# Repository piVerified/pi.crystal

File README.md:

# pi.crstal

A blinker board that is in thw shape of a crystal! 

---
## 3D

| Top | Bottom |
| :--: | :--: |
|  |  |

---
## KiCAD

| Schematic | PCB |
| :-------: | :-: |
|  | |

---
# BOM
|Name                                       |Purpose                                            |Quantity|Total Cost (USD)|Link                                                                                                                                                                                                                   |Distributor     |
|-------------------------------------------|---------------------------------------------------|--------|----------------|-----------------------------------------------------------------------------------------------------------------------------------------------------------------------------------------------------------------------|----------------|
|PCB (minimum order qty is 5)               |Main Circuitry                                     |5       |10.27           |https://robu.in/cart                                                                                                                                                                                                   |Robu            |
|Jumper Wires (pack of 40)                  |To program the IC via a breadboard and rp2040 setup|1       |0.54            |https://quartzcomponents.com/products/male-to-male-connecting-wires-jumper-wires-set-of-40?variant=45062845464810                                                                                                      |Quartzcomponents|
|CR2032 Battery Button Cell Holder - 20mm   |For hold the cell                                  |5       |0.65            |https://quartzcomponents.com/products/cr2032-battery-button-cell-holder-20mm?variant=45714349555946                                                                                                                    |Quartzcomponents|
|LDR Sensor (Light Dependent Resistor) - 5mm|Acts as a interface button                         |10      |0.50            |https://quartzcomponents.com/products/ldr-light-dependent-resistor-5mm?variant=31898051543175                                                                                                                          |Quartzcompenets |
|ATTINY85-20U                               |To intiate the blinig sequence                     |2       |5.08            |https://quartzcomponents.com/products/attiny85-8-bit-avr-microcontroller?variant=33590640345223                                                                                                                        |Quartzcompenets |
|Resistor (pack of 50)                      |to protect the led from current spikes             |1       |1.50            |https://www.flipkart.com/samaes-50-pics-10-ohm-1-watt-5-resistors-fixed-resistor/p/itm472d700363929?pid=RESG6HFFYTRZVUPM&lid=LSTRESG6HFFYTRZVUPM869DSI&marketplace=FLIPKART&pageUID=1775637263894                      |Flipkart        |
|Coin Cell (pack of 5)                      |to power the ckt                                   |1       |1.66            |https://www.flipkart.com/panasonic-cr-2032-battery/p/itmbd0412fc6ad6a?pid=ACCFZJTYAUTKVAUW&lid=LSTACCFZJTYAUTKVAUWVO1CZP&marketplace=FLIPKART&pageUID=1775637143852                                                    |Flipkart        |
|8mm pink led (pack of 100)                 |blinker lights                                     |1       |1.93            |https://www.flipkart.com/wizzo-100-pcs-transparent-pink-led-8mm-3v-dc-2-pin-light-electronic-hobby-kit/p/itmaf0b9e78784ea?pid=EHKH3FCSAGTEZKTE&lid=LSTEHKH3FCSAGTEZKTELBYI07&marketplace=FLIPKART&pageUID=1775284472455|Flipkart        |

---
# Softwares Used

* KiCAD -> PCB Design
* Arduino IDE -> Firmware

---
# Bibliography

> This project would not have been possible without the help of the amazing people of the internet, the Hack Club Stasis Guide, and a bit of AI.

> PS: Hugely inspired by @darizone's Firefly kit

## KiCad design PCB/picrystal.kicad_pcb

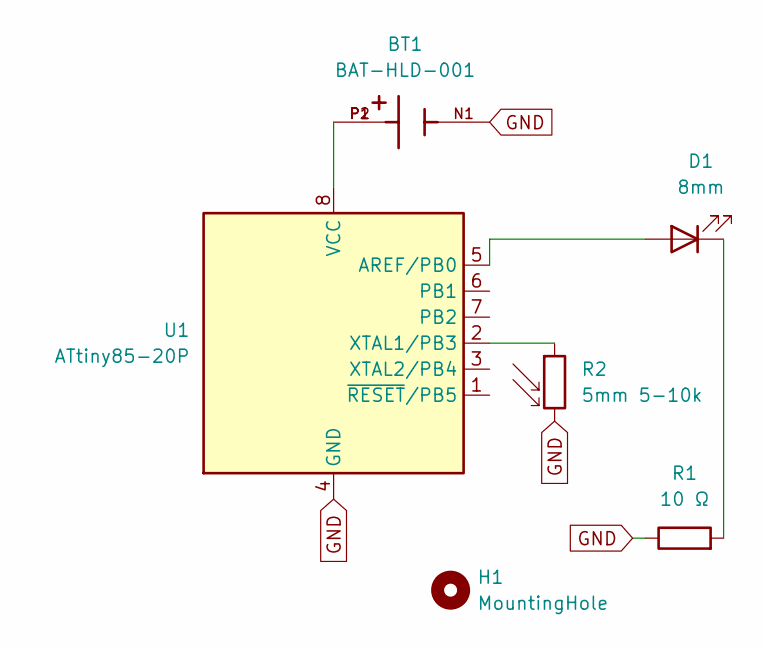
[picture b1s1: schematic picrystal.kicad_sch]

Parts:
BT1: BAT-HLD-001; BAT_BAT-HLD-001; PARTREV C
D1: 8mm; LED_D8.0mm
H1: MountingHole; MountingHole_6mm
R1: 10 Ω; R_Axial_DIN0207_L6.3mm_D2.5mm_P7.62mm_Horizontal
R2: 5mm 5-10k; R_LDR_5.0x4.1mm_P3mm_Vertical
U1: ATtiny85-20P; DIP-8_W7.62mm

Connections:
GND: BT1.N1, R1.1, R2.2, U1.4 (GND)
unnamed: D1.2 (A), U1.5 (AREF/PB0)
unnamed: D1.1 (K), R1.2
unnamed: BT1.P1, BT1.P2, U1.8 (VCC)
unnamed: R2.1, U1.2 (XTAL1/PB3)

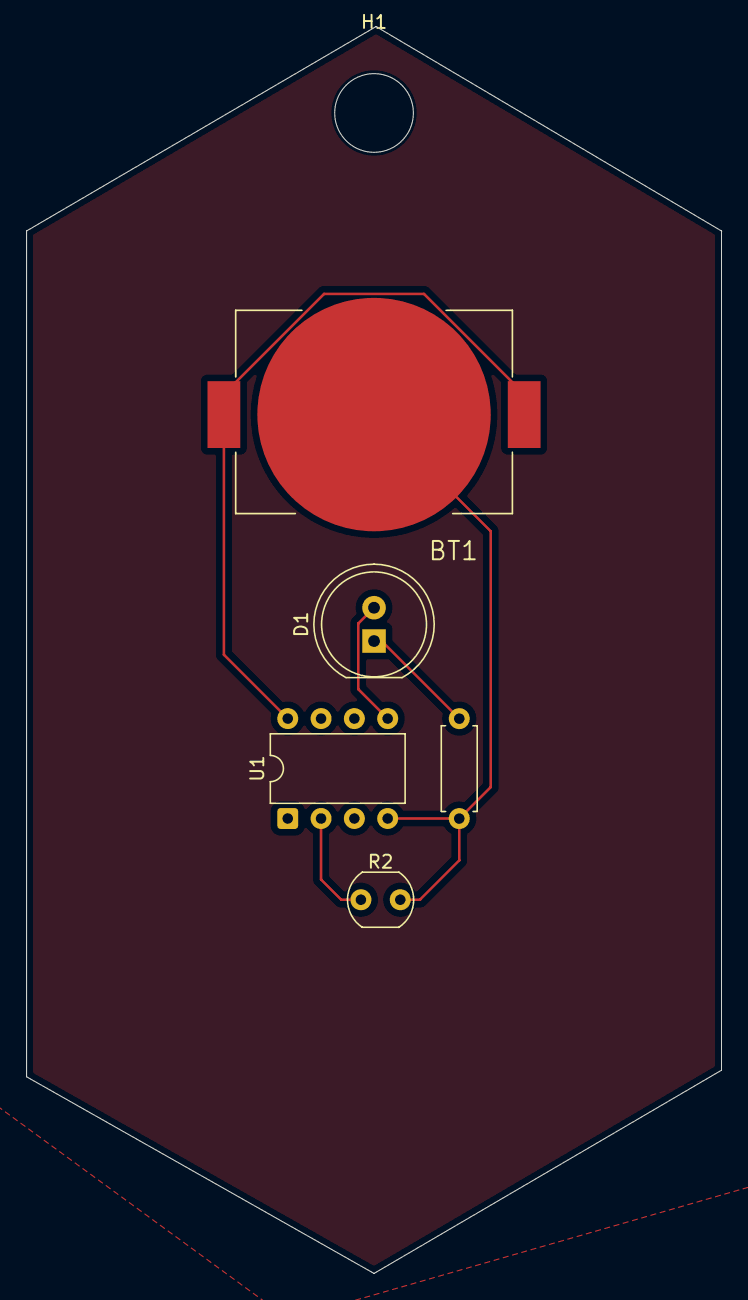
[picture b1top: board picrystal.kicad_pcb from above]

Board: 2 copper layers, 53.0 x 95.1 mm, 6 parts (0 on the bottom side), 5 nets.

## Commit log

2026-04-04 Rename project to pi.crstal and update details
    Updated project name and description in README.md.
2026-04-08 Revise README content and correct formatting
    Updated README.md to improve clarity and add details.
